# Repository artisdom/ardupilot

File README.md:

A Fork of Ardupilot for a barebones STM32 running FreeRTOS and an onChip OSD
----------------------------------------------------------------------------

BuildInfo
---------

Building apm_quantracker
TODO export env vars
export QUAN_TARGET_VEHICLE=QUAN_APM_ARDUPLANE
export QUANTRACKER_ROOT_DIR=<path to quantracker>

need GNU awk

Dependencies
------------

The dependencies can be retrieved on linux by downloading building and running the installer
air_installer from github.

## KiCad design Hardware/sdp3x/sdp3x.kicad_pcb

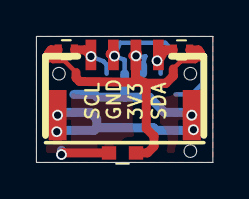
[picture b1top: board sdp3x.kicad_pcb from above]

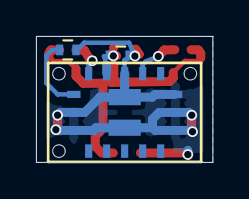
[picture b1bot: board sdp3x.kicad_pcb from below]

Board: 2 copper layers, 9.8 x 7.0 mm, 7 parts (3 on the bottom side), 5 nets.

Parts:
C1: C; C_0402
C2: C; C_0603
J1: Conn_01x04; JST_GH4_vert
R1, R2, R3: R; R_0402
U1: SDP3x_I2C; SDP3x_i2c

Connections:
/SCL: J1.1, R2.2, U1.5
/SDA: J1.4, R1.2, U1.8
/VDD: C1.1, C2.1, J1.3, R1.1, R2.1, U1.7
GND: C1.2, C2.2, J1.2, R3.2, U1.1, U1.2, U1.3, U1.6, U1.10, U1.11
unnamed: R3.1, U1.9

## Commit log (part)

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2016-11-22 now working without extra writes hooray!
2016-11-22 toggle which uart is used for output, console easier for debugging, but telem easier for testing!
2016-11-22 tidy up a little
2016-11-23 added functions to ask if the eeprom write queue is flushed out to th eeprom and to wait for it to be flushed
2016-11-23 modify the test for a larger input string. Requires to test that the eeprom write buffer has been flushed, else the read may return what was on the eeprom before the write buffer has been flushed to 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
2016-11-23 moved ins generic and StorageManager from examples to test dir
2016-11-23 move quan examples to quan test
2016-11-23 temporarily put gps on uart4 as connector for uart3 is reversed
2016-11-23 AHRS_Test working OK so that is a good sign
2016-11-24 modify the directions of mag and imu
2016-11-25 make quan storage funs take 32 bits so can access higher eeprom area
2016-11-25 set offsets to 0, todo, read from higer eeprom
2016-11-25 add compass cal useractive
2016-11-25 mods to AHRS but doesnt seem to have correct gains
2016-11-25 get example building ok
2016-11-25 i2c init is done in scheduler but may cause issues for quantracker board
2016-11-25 remove aerflite defines since it use another src file
2016-11-25 looks like rx dam only isnt working, so back to irqs. TODO put TX dma back
2016-11-25 ad diagnostic for compass cal fail
2016-11-25 add board include guards
2016-11-26 add on_telemetry_transmitted for quan build
2016-11-26 get binary name right
2016-11-26 lots of problems with storage
2016-11-26 make read booleanret, doing nothing is ok
2016-11-26 put ee read in the q for now, slow but deterministic
2016-11-26 get eeprom storage stress test working
2016-12-01 whitespace only
2016-12-01 add battery voltage to OSD
2016-12-03 update airspeed for quan
2016-12-03 display adc values on osd in test
2016-12-03 udate AHRS with mk2 board compass offsets, and remove the non quan stauff. Now battery voltage and airspeed are showing on the osd
2016-12-05 add baro altitude to osd variables, tested in AHRS test
2016-12-05 renam AHRS_Test to AHRS and renam main cpp file
2016-12-05 remove DMA debug from analogin
2016-12-05 rename AP-BattMonitor_test.cpp to main.cpp
2016-12-05 more test file renaming
2016-12-06 Full ArduPlane app now runs. Looks like there is a call of ap_hal.i2c ptr somewhere. Anyway it runs, but no RC Out and eeprom params dont load or save
2016-12-06 add a test of AP_Param since it isnt working ATM
2016-12-06 add bo lreturns and better debug diagnostics coverage to AP_Param
2016-12-06 add conditional board defines so that these files arent built for quan
2016-12-06 add more diagnostics to params load. N.B. TODO uncomment the erase_all functionality for new boards
2016-12-06 add rc out to rc in test. Really needs a warning or option here to avoid bad things
2016-12-06 comment out diagnostic when enabling and diabling rc outputs
2016-12-08 verbose build
2016-12-08 some slight mods to osd output text for init
2016-12-08 add the telemtry tx functionality toardupilot aerflite, bench tested and seesm to work with latest quan
2016-12-08 add teme to aerflite, note not working atm, but prob an issue in quantracker for aerflite
2016-12-29 remove run time gain and change sign of LIS3MDL outputs to ArduPilot compass frontend
2016-12-30 LIS3MDL compass: reverse the y output.With this etting,the compass now performs corectly for aerflite, as shown on the osd and in APM planner, once it has been calibrated. Else the gyro will work cor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
2017-01-04 comments and spacing only
2017-01-04 eeprom flush function only for aerflite
2017-01-04 for clear dma flags use assign not or_assign
2017-01-04 eeprom flush only for aerflite
2017-01-07 remove dodgy millis_from_isr, will replace with a better taolred option
2017-01-08 comment out the compass save offsets every minute, which causes the arduplane thread to stall for some seconds. It may be possible to do this better. One option is to save to a file in flight, or eve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
2017-01-08 remove the micros_from_isr function, use the freertos timer for the functionality instead
2017-01-15 remove unused submodules
2017-01-15 comments and tidying up only
2017-02-17 add gps_status to osd telemetry output, but not tested yet
2017-02-17 remove AP_HALL_CLASS define from hal_boards header and remove navekf and navekf2 for now
2017-02-18 remove other vehicles than plane for now
2017-02-18 add clean to ahrs test makefile
2017-02-18 remove anything defined inside if defined AP_AHRS_NAVEKF_AVAILABLE
2017-02-18 remove lots of extraneous matter
2017-02-18 update freertos on travis
2017-02-18 ws only
2017-02-18 remove parachute functionality
2017-02-18 move the exposed data around. Make the channel id const
2017-02-19 RC_Channel: make the pwm_out variable private
2017-02-19 camera only needs aux rc channels
2017-02-19 Remove RC_Channels_aux. N.B. Still lots of mixing junk in there so needs work yet
2017-02-19 remove rudder_only ee_parm. we will use a mixer for that
2017-02-19 remove several mixing eeparams and fix up
2017-02-19 remove plane redundant elevon variables
2017-02-19 remove apm_pi lib
2017-02-19 make more rc_channele stuff private
2017-02-19 more rc_Channel pruning
2017-03-06 change RC_Channel radio_out to a private m_radio_out and use member functions to access
2017-03-07 remove relay and put rc trim and min max in functions
2017-03-07 remove the SERVO_MAX define from defines.h
2017-03-07 make cr_channel set_default_dead_zone argless, since the value is only ever updated by the constant
2017-03-07 remove redundant include
2017-03-08 remove rudder_input variable and read ruuder direct we hope!
2017-03-08 instead of accesing hal. rcout directly to demo_servos use the existing API, since otherwise it wont work with mixer
2017-03-09 Remove the RC_Channels static array place direct instances of RC_Channel in Plane for pitch roll yaw throttle rather than pointers. Eventually this will be removed entirely. Untested as yet
2017-03-09 remove a little bit more cruft from rc channels
2017-03-10 moved some function definitions around for clarity
2017-03-10 Remove the pwm (throttle) argument to Plan::control_failsafe. pwm causes no side-effects except for output as a status message to mavlink.
2017-03-10 change rc_failsafe_active to failsafe_state_detected
2017-03-10 Simplify the comtrol_failsafe logic. Really needs to be sorted into failsafe on no rc and failsafe on throttle low. Maybe they resolve to the same thing but the THR_Failsafe param shoudl be renamed t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
2017-03-10 remove rc_ch x fro parameters. Dont know if they will be inited now but sort that later make set_radio_in and set_control_in private. Redo the failsafe fun with public funs. (add special case set_con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
2017-03-10 remove the runtime type change for RC_Channels. Make the type a ctor arg for now. In fact throttle could be an enirely separate class, as could pitch yaw roll. Remove runtime update. Though the idea 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
2017-03-10 remove dead code redo stabilize_stick_mixing_direct, same logic but dif style remove throttle slew_limit last throttle arg and keep a local state variable last_throttle
2017-03-11 remove eeprom min max and trim. Prob only trim required will have to think how it works
2017-03-11 do in class init of RC_Channels
2017-03-11 make the set_pwm fun private and use some public joystick abstractions instead
2017-03-11 remane radio_out to ouput locally as a start
2017-03-11 rename channel_rudder to channel_yaw
2017-03-11 replace throttle with thrust
2017-03-11 rename various function and add a testsuite tested in AP_HAL_Quan/test/RC_Channels
2017-03-12 redo stick mixing to use norm_input redo logic in calc_thrust, a bit neater Use thrust_off function rename var in update_load_factor
2017-03-12 add linendings on param commnets
2017-03-12 continue splitting RC_Channel into separte parts. Now have a joystickinput, a fc_input and a fc_output
2017-03-13 Pretty messy but hope that basics of generic mixing are in there for arduplane. Needs much checking and testing though
2017-03-17 mixer installed in arduplane. N.B that mixer lib is local file path atm
2017-03-18 upgrade to newer mixe lang api. Implement reqd functions
2017-03-19 remove the old crtn and crti libs. Neede for init and fini, but works ok by removing -nostartfiles from link flags
2017-03-19 mods to get building with gcc6
2017-03-20 enable servo outputs. Ideally there should be some means to say what are throttle outputs or just keep them at zero while disarmed
2017-03-20 change sign of gains for aerflite Falcon wing elevons
2017-03-20 add mixer_lang to travis build
2017-03-24 comment out the debugging printfs and setup reverse yaw in only for sitl
2017-03-31 build ok using sitl
2017-03-31 commentets only
2017-04-03 solve osd bug in get_bearing_and_dist. Convert angle to different units else get incorrect value of dista nd bearing home
2017-04-04 updatestick input sense for sim
2017-04-04 clean up after clean_mixing-sitl merge
2017-04-04 problem was in constarin of throttle slew rate, min and max reversed
2017-04-04 tidy up after devel merge
2017-04-15 add 7th rc output channel
2017-04-17 Final adjustments to SkyHook Disco mixer to get working for maiden flight
2017-04-29 skyhook disco sim mixer script with crow. Tested in mixer_gui only
2017-05-04 make flap centre in other than manual modes. Adjust elevator trim in croe mode to give much more down. Make the crow variables parametric on horn length. Not tested yet
2017-05-05 put mixers in separate files
2017-05-07 notes about compasss setting
2017-05-08 add rf modem output of gps info for tracker
2017-06-18 rewrite schematic, did ERC and DRC, but no real changes
2017-06-19 use both TX and RX dma for imu spi
2017-06-19 update Aerflite version
2017-06-19 in i2c irqs, disable interrrupt before reading status flag
2017-07-08 add altitude scale down right hand side, tested but not with actual altitude data
2018-01-22 adjust osd altitude scale
2018-03-24 added socket connection to flightgear viewer at 127.0.0.1:5503
2018-03-25 remove AC_AttitudeControl lib
2018-03-26 AP_Param: fix printf warning
2018-03-26 remove AP_HAL_Linux
2018-03-26 remove hal_fly_maple lib
2018-03-26 remove libs ac_preclan,ac_pid,ac_sprayer
2018-03-26 remove AC_WPNav
2018-03-29 move default location, n.b this overrides command line
2018-03-29 sanitise ap_baro
2018-03-30 getting sitl building with travis v3
2018-03-30 get sitl building with travis v2
2018-03-30 more sanittise ap_baro
2018-03-30 get quan-ahrs-test running
2018-03-30 Add tenttaive fg io xml
2018-03-31 ap_ahrs: move defines to source
2018-03-31 ap_airspeed : move defs to correct class files, adjust order of includes in class h
2018-03-31 simplify build system
2018-03-31 remove unrelated info
2018-04-03 remove unused file
2018-04-03 update flightgear_out.xml to include timing
2018-04-04 streamline ap_baro and ap_inertialsensor
2018-04-04 ap_inertial_sensor: replces defines with constexpr etc
2018-04-04 ap_compass: tidy up
2018-04-04 ap_inertial_sensor: remove singleton stuff, and add missing include for test
2018-04-05 make some ap_param stuff protected and replace defines with constants
2018-04-05 ap_airspeed: provide similar interface to other sensors
2018-04-05 ap_inertial_sensor : change create to connect
2018-07-14 add info on i2c addresses
2018-07-14 add current sensor and airspeed sensor pcbs
2018-07-15 add initial sdp3x airspeed code, just a whoami test atm
2018-07-16 i2c eeprom read to flags in on_writ_last_byte_transfer_complete
2018-07-16 remove valid heap me fun
2018-07-16 compile i2c read write driver
2018-07-17 sdp3x sensor added. N.B there is a i2c glitch very occasinally which must be found and fixed before flying this
2018-07-17 add global get_barometer function
2018-07-18 add clear i2c bus error to i2c_periph
2018-07-18 update i2c task loop. Improve error correction a little
2018-08-16 sd3p airspeed sensor make compilation of source conditional
2018-08-16 AP_Compass : comments only
2018-08-16 change airspeed font back to small font
2018-08-17 Tranquility mixer : reduce aileron gain and use symbolic constants for v tail pitch and yaw gain. Increase pitch gain and reduce yaw gain. Reduce rudder_to roll gain
2018-08-17 HAL_Quan::RcInput: comments only
2018-08-18 ArduPlane.cpp : comments only
2018-08-18 ArduPlane control modes: work on simplifying failsafe logic
2018-08-18 Geofence: add plane functions only if geofence is defined
2018-08-19 simlify control modes, wip
2018-08-19 add battery low and no radio messsages to osd
2018-08-20 move enqueu batt voltage til the var has been initisled from eeprom!
